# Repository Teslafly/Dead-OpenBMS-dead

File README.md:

THIS PROJECT IS DEAD. The avalibility of other projects and low cost off the shelf solutions has imporved significantly to where this project is no londer needed.

A much more mature open source bms that I recommend is https://github.com/EnnoidMe/ENNOID-BMS that has all the features that I had wanted to implement.
Off the shelf hardware is available for that too if you don't want to build your own.

Intro
==========
* This project aims to create an open source, scalable Battery management system for use in just about anything with more than 4 lithium batteries. (and currently up to 96 cells without a second master board)
* It aims to be as open source as possible so ideally all software should be free and unlimited. All PCB designs are done in KiCad (Using Fairly recent dev builds through Kicad Winbuilder) and all microcontroller programming is done in Arduino.

You can find a discussion thread for this project here on the Endless Sphere fourm: http://endless-sphere.com/forums/viewtopic.php?f=14&t=63863
Goals
==========
* Open source - It seems that almost all gms systems on the market are closed down these days. we want to be able to add whatever features we please as the EV world gets ever more integrated and complex
* Low cost - The BMS IC was selected to be as low cost as possible with a daisy chain approach used to further attempt to reduce costs through high manufacturing volume. Goal of $2 per cell can be reached. Master board may bump that up for smaller systems.
* Reliable - Even though a goal is to keep costs low, reliability should not be unnecessarily decreased for small cost improvements
* Safe - in going with reliable, I don't want this thing to start any fires or cause any damage. I want it to prevent any possible catastrophes associated with using such a power dense energy source.
* Easy to use - Board is programmed in the commonly known Arduino, but may use an rtos like chibios to facilitate low power-modes and can/usb tasks. Integration with a larger system could possibly be done with ladder logic programming.
* Multi chemistry - Can monitor and balance almost anything with "lithium" in the name. (lipo, lifepo4, etc. Possibly even super-capacitor banks)

Boards
===============
There are several boards contained within this project

* The Master board. it contains the mcu (The same microcontroller used in the teensy 3.1) The CAN transceiver and a couple other odds and ends such as a contactor driver.
* The MicroMaster board. This one contains an atmega328 with current sensing and little else. 
This board is meant as a lower cost alternative to the regular master board. It can also be used to control packs >96 cells by connecting it to a master via optoisolators.
* The daughter cell management board. It contains the voltage measuring ic and balancing resistors.
* The bus termination board. This one does precious little except ties the datapins of the top slave board together and allow activation of the system with an optoisolator.

Master Features (plannned)
===============
* Teensy 3.1 microcontroller (MK20DX256VLH7)
* USB programmable with a possibility of usb otg for android devices / dashboards. (and could charge phones/tablets with switching regulator)
* CAN transceiver for data connection to other modules.
* Connectors for an i2c/serial LCD dashboard and all extra pins broken out for auxiliary I/O.
* Input voltage sensing
* Switching voltage regulator to bring pack voltage down to 5-12v when system is on for auxiliary functions.
* 4 mosfet controlled low side outputs. These can be used to control a contactor, precharge circuit relay, fan, etc.
* 3 dedicated current sensor inputs. one for charging, one for the motor and one on-board for monitoring auxiliary systems.
* SD card slot for datalogging (and possible configuration via txt file)
* Analog and pwm throttle input & output. This can map the throttle to different values, change a analogue signal to a pwm one, or/and cut/hold back throttle when the pack is almost empty/dead.
* Opto isolators for controlling charger or communicating to voltage shifted masters.
* Buzzer / alarm - If something goes severely wrong, this board will let you know

MicroMaster Features - Implemented
===============
* Atmega328 main processor @ 3.3v - 8mhz. Programmable through arduino with usb -> serial adapter (Program it just like an Arduino pro mini)
* Runs completely off power output from slave board/s. This is convenient but allows no SD card or indicator leds as the ATA6870N can only supply 20ma
* 2 dedicated current sensor inputs. Useful for sensors like the ACS759
* 2 auxiliary 12-24v 5A NPN mosfets. (current is untested!) The voltage on this auxiliary rail is also monitored via a voltage divider. This is for controlling contactors, fans, etc
* 1 connector for a precharge circuit. Outputs for 1 small relay and a protected adc input for a controller voltage monitoring circuit.
* All other I/O pins are brought out to a 10 pin header along with 3.3v and GND. 

Slave Board Features (plannned)
===========
* Measures 4-6 Li-Ion Cells in Series 
* Stackable Architecture Enables >400V Systems (Up to 16 6s modules)). - (Micro)Master modules can be isolated and daisy chained  for even higher voltages 
* 0.25% Maximum Total Measurement Error (12 bit adc) - This will be tested in reality once the first boards are constructed.
* Extremely low power when asleep. (<100ua)
* Two Thermistor Inputs - One connected to an On-Board Temperature Sensor and the other one brought out to a header.
* temperature management. software will reduce the duty cycle of the balance resistors if the board gets too hot.

Cell Balancing:
==============
* Balancing achieved with ~20 ohm resistor banks. This means ~1 watt power of dissipation per cell. Heatsinking is probably needed at this level for full balancing current on all cells.
* An onboard thermistor will instruct the controller to reduce the duty cycle of the resistors in 25% increments (from 25-100%) to keep the board from overheating / melting.
* Predictive cell balancing? If a cell always needs a certain amount of energy removed while charging the board will pre-emptively balance the cell. I know of no example of this and will investigate its utility 

Software Goals
===========
* ~Readout of all individual cell voltages and analog inputs ~ DONE! (It could probably be made more efficient though)
* Manually control system outputs 
* Dataloggging, including current, cell voltages, and recording of total time the balance resistor has been on for each cell. useful for identifying weak/strong cells.
* Cell resistance estimate - use amperage draw and cell voltages to estimate cell resistances.
* Coulomb Counting for entire battery pack as well as cumulative coulumbs in/out for battery wear estimation

Photos
===========

![schematic] (https://raw.githubusercontent.com/Teslafly/OpenBMS/master/Docs/photos/Open%20source%20BMS.png)

TODO:
===============
* finish and post the micromaster board -Done!
* make a separate folder for all the kicad libraries and 3d models used in the project
* write a blog post on teslafly.wordpress.com detailing this project.
* make some prototypes ~ parts have arrived.

License
===========
GPL 3.0

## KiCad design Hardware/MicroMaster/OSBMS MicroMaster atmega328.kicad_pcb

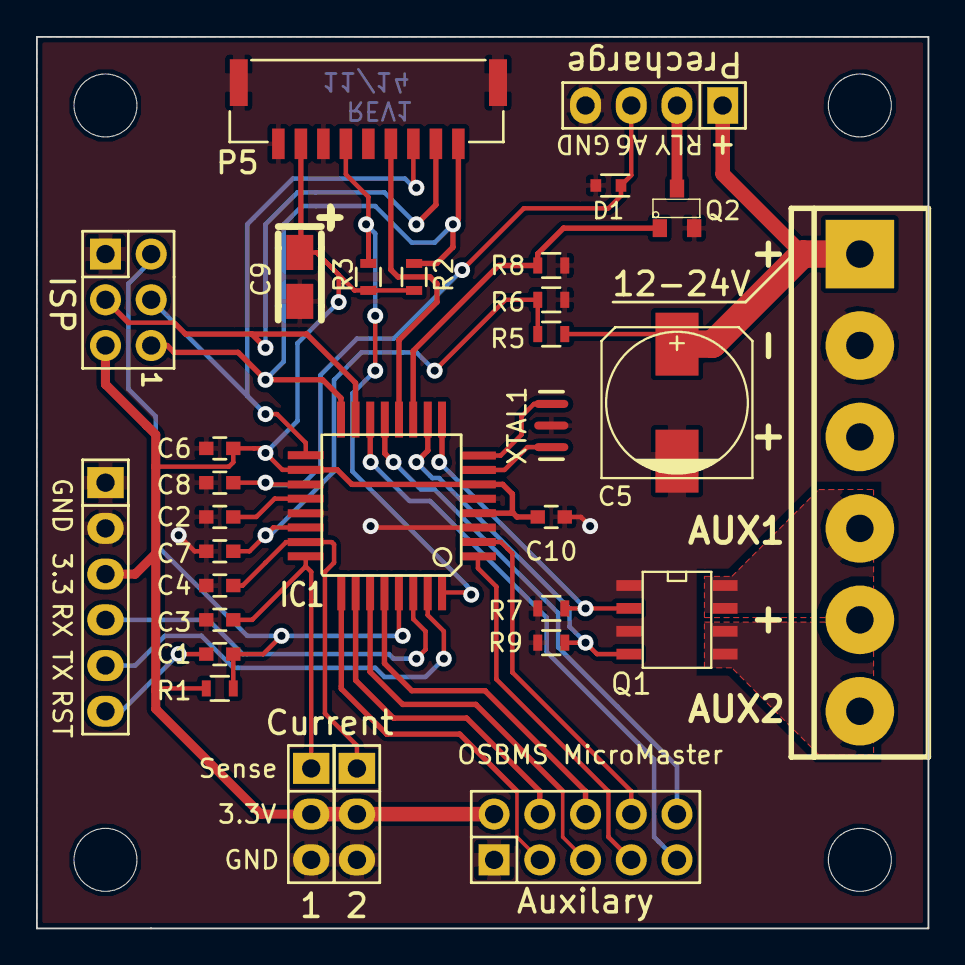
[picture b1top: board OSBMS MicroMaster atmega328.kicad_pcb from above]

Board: 2 copper layers, 49.5 x 49.5 mm, 35 parts (0 on the bottom side), 33 nets.

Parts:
C1, C2, C3, C4, C6, C7, C8: 100NF; C_0603
C5: CP1; c_elec_8x10
C9: 33uF PolC; TantalC_SizeA_EIA-3216_Reflow
C10: 100nF; C_0603
D1: 3.3vZENER; SOD-523
IC1: ATMEGA328P-A; TQFP-32
MH: MountingHole_3-5mm_RevA_Date21Jun2010; MountingHole_3-5mm
MH#2, MH#3, MH#4: MountingHole_3-5mm_RevA_Date21Jun2010; MountingHole_3-5mm
P1: CONN_01X06; Pin_Header_Straight_1x06
P2: CONN_02X03; Pin_Header_Straight_2x03
P3, P4: CONN_01X03; Pin_Header_Straight_1x03
P5: CONN_01X09; Connector_SMD_GH_SIDECONN_1X9_1.25MM
P6: CONN_01X10; Pin_Header_Straight_2x05
P7: CONN_01X06; bornier6
P10: CONN_01X04; Pin_Header_Straight_1x04
Q1: FDS6892A; SOIC-8-W
Q2: BSS138; SOT-23
R1, R2, R3, R7, R8, R9: 10K; R_0603
R5: 50k ohm; R_0603
R6: 5k ohm; R_0603
XTAL1: 8mhz resonator; RESONATOR-SMD-mutera

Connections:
400khz_clk: IC1.13, P5.5
+3.3V: C6.2, C9.1, C10.1, IC1.4, IC1.6, IC1.18, P1.3, P2.5, P3.2, P4.2, P5.8, P6.2, R1.2, R2.1, R3.1
+12V: C5.1, P7.1, P7.3, P7.5, P10.1, R5.2
/S-RST: C1.1, P1.6
A0: C4.2, IC1.23, P4.1
A1: C3.2, IC1.24, P3.1
A2: IC1.25, P6.3
A3: IC1.26, P6.4
A6: C8.2, D1.2, IC1.19, P10.3
A7: C7.2, IC1.22, R5.1, R6.2
CS_N: IC1.12, P5.4
D3*: IC1.1, P6.7
D4: IC1.2, P6.8
D5*: IC1.9, Q1.2, R7.2
D6*: IC1.10, Q1.4, R9.2
D7: IC1.11, Q2.1, R8.2
D10*: IC1.14, P6.9
GND: C2.1, C3.1, C4.1, C5.2, C6.1, C7.1, C8.1, C9.2, C10.2, D1.1, IC1.3, IC1.5, IC1.21, P1.2, P2.1, P3.3, P4.3, P5.7, P5.9, P6.1, P7.2, P10.4, Q1.1, Q1.3, Q2.2, R6.1, R7.1, R8.1, R9.1, XTAL1.2
Int0/2: IC1.32, P5.6, R3.2
MISO: IC1.16, P2.6, P5.1, R2.2
MOSI: IC1.15, P2.3, P5.2
unnamed: C2.2, IC1.20
unnamed: IC1.7, XTAL1.3
unnamed: IC1.8, XTAL1.1
unnamed: P7.4, Q1.7, Q1.8
unnamed: P7.6, Q1.5, Q1.6
unnamed: P10.2, Q2.3
RESET: C1.2, IC1.29, P2.2, R1.1
RXD: IC1.30, P1.4
SCK/13: IC1.17, P2.4, P5.3
SCL/A5: IC1.28, P6.6
SDA/A4: IC1.27, P6.5
TXD: IC1.31, P1.5

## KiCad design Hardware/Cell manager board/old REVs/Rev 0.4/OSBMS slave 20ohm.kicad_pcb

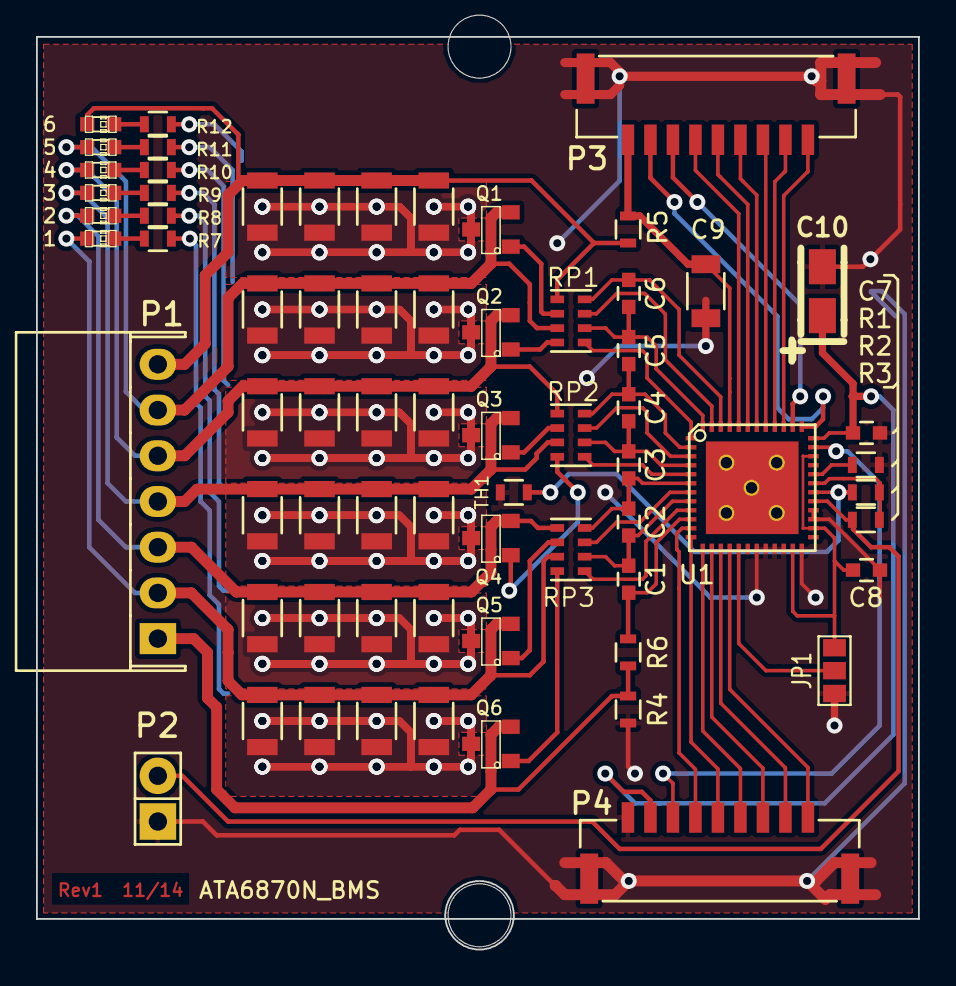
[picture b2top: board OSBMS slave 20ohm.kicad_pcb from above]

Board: 2 copper layers, 49.0 x 50.7 mm, 76 parts (1 on the bottom side), 63 nets.

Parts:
28 mil Id via, 28 mil Id via#2, 28 mil Id via#3, 28 mil Id via#4, 28 mil Id via#5: via; 35-Od-28mil-Id-via
C1, C2, C3, C4, C5, C6, C7, C8: 100nF; C_0603
C9: 10uF PolC; C_1206
C10: 33uF PolC; TantalC_SizeA_EIA-3216_Reflow
D1, D2, D3, D4, D5, D6: LED; LED-0603
JP1: JUMPER3; GS3
MH: MountingHole_3-5mm_RevA_Date21Jun2010; MountingHole_3-5mm
MH#2: MountingHole_3-5mm_RevA_Date21Jun2010; MountingHole_3-5mm
P1: CONN_01X07; Shrouded_Header_Angled_1x07
P2: EXT-TMP; Pin_Header_Straight_1x02
P3, P4: CONN_01X09; Connector_SMD_GH_SIDECONN_1X9_1.25MM_45515711ND
P5: CONN_01X01; 1Pin
Q1, Q2, Q3, Q4, Q5, Q6: BSS138; SOT-23
R1: 121KΩ; R_0603
R2, R3: 10KΩ; R_0603
R4, R5: 10Ω; R_0603
R6: 1K; R_0603
R7, R8, R9, R10, R11, R12: 100Ω; R_0603
R13, R20, R21, R22, R23, R24, R25, R26, R27, R28, R29, R30, R31, R32, R33, R34, R35, R36, R37, R38, R39, R40, R41, R42: 82.5Ω; R_1206
RP1, RP2, RP3: 1K_PACK; R_Cat16-4
TH1: THERMISTOR; R_0603
U1: ATA6870N_BMS; QFN-48-1EP

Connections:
+3.3V: C7.1, C10.1, P4.2, U1.36
+BATT: C9.1, P3.9, R5.1, U1.45
/DISCH1: RP3.5, U1.9
/DISCH2: RP3.7, U1.7
/DISCH3: RP2.5, U1.5
/DISCH4: RP2.7, U1.3
/DISCH5: RP1.5, U1.1
/DISCH6: RP1.7, U1.47
GND: C7.2, C8.2, C9.2, C10.2, JP1.3, P2.1, P4.1, R1.1, R4.1, TH1.2, U1.19, U1.20, U1.21, U1.22, U1.24, U1.27, U1.28
unnamed: C1.1, C2.2, RP3.6, U1.8
unnamed: C1.2, R6.1, U1.10
unnamed: C2.1, C3.2, RP3.8, U1.6
unnamed: C3.1, C4.2, RP2.6, U1.4
unnamed: C4.1, C5.2, RP2.8, U1.2
unnamed: C5.1, C6.2, RP1.6, U1.48
unnamed: C6.1, RP1.8, U1.46
unnamed: C8.1, JP1.1, U1.23, U1.26, U1.34
unnamed: D1.1, P1.7, R5.2, R20.1, R21.1, R22.1, R23.1, RP1.1
unnamed: D1.2, R12.2
unnamed: D2.1, P1.6, Q1.2, R24.1, R25.1, R26.1, R27.1, RP1.3
unnamed: D2.2, R11.2
unnamed: D3.1, P1.5, Q2.2, R28.1, R29.1, R30.1, R31.1, RP2.1
unnamed: D3.2, R10.2
unnamed: D4.1, P1.4, Q3.2, R13.1, R32.1, R33.1, R34.1, RP2.3
unnamed: D4.2, R9.2
unnamed: D5.1, P1.3, Q4.2, R35.1, R36.1, R37.1, R38.1, RP3.1
unnamed: D5.2, R8.2
unnamed: D6.1, P1.2, Q5.2, R39.1, R40.1, R41.1, R42.1, RP3.3
unnamed: D6.2, R7.2
unnamed: JP1.2, U1.17
unnamed: P1.1, Q6.2, R4.2, R6.2
unnamed: P2.2, R3.2, U1.29
unnamed: P3.1, U1.39
unnamed: P3.2, U1.40
unnamed: P3.3, U1.41
unnamed: P3.4, U1.42
unnamed: P3.5, U1.43
unnamed: P3.6, U1.44
unnamed: P3.7, U1.38
unnamed: P3.8, U1.37
unnamed: P4.3, U1.35
unnamed: P4.4, U1.11
unnamed: P4.5, U1.12
unnamed: P4.6, U1.13
unnamed: P4.7, U1.14
unnamed: P4.8, U1.15
unnamed: P4.9, U1.16
unnamed: Q1.1, RP1.2
unnamed: Q1.3, R12.1, R20.2, R21.2, R22.2, R23.2
unnamed: Q2.1, RP1.4
unnamed: Q2.3, R11.1, R24.2, R25.2, R26.2, R27.2
unnamed: Q3.1, RP2.2
unnamed: Q3.3, R10.1, R28.2, R29.2, R30.2, R31.2
unnamed: Q4.1, RP2.4
unnamed: Q4.3, R9.1, R13.2, R32.2, R33.2, R34.2
unnamed: Q5.1, RP3.2
unnamed: Q5.3, R8.1, R35.2, R36.2, R37.2, R38.2
unnamed: Q6.1, RP3.4
unnamed: Q6.3, R7.1, R39.2, R40.2, R41.2, R42.2
unnamed: R1.2, U1.32
unnamed: R2.1, R3.1, U1.31
unnamed: R2.2, TH1.1, U1.30
ThermalGnd: 28 mil Id via.1, 28 mil Id via#2.1, 28 mil Id via#3.1, 28 mil Id via#4.1, 28 mil Id via#5.1, P5.1

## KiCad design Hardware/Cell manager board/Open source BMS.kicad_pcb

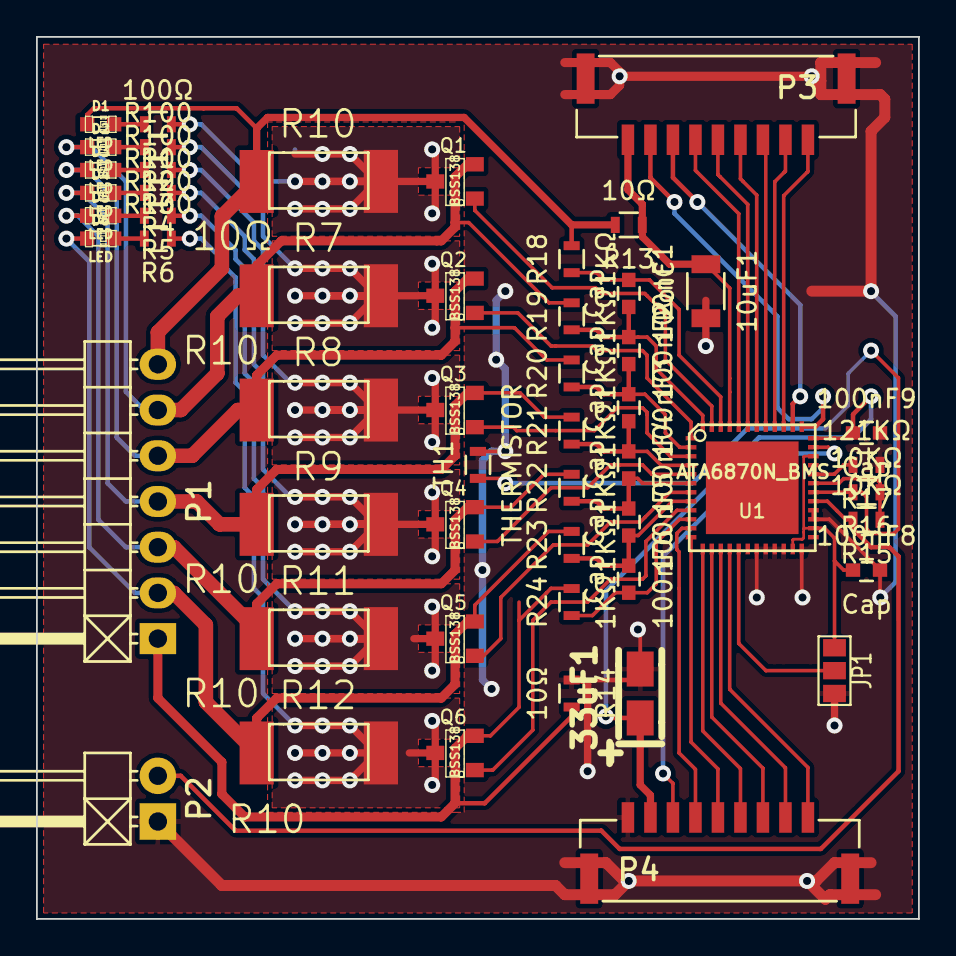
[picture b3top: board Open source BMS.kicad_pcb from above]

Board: 2 copper layers, 49.0 x 49.0 mm, 53 parts (0 on the bottom side), 56 nets.

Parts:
10uF1: PolC; C_1206
33uF1: PolC; TantalC_SizeA_EIA-3216_Reflow
100nF1, 100nF2, 100nF3, 100nF4, 100nF5, 100nF6, 100nF8, 100nF9: Cap; C_0603
D1, D2, D3, D4, D5, D6: LED; LED-0603
JP1: JUMPER3; GS3
P1: CONN_01X07; Pin_Header_Angled_1x07
P2: EXT-TMP; Pin_Header_Angled_1x02
P3, P4: CONN_01X09; Connector_SMD_GH_SIDECONN_1X9_1.25MM_45515711ND
Q1, Q2, Q3, Q4, Q5, Q6: BSS138; SOT-23
R1: 100Ω; R_0603
R2, R3, R4, R5, R6: R100; R_0603
R7, R8, R9, R11, R12: R10; R_3521
R10: 10Ω; R_3521
R13, R14: 10Ω; R_0603
R15, R16: 10KΩ; R_0603
R17: 121KΩ; R_0603
R18, R19, R20, R21, R22, R23, R24: 1KΩ; R_0603
TH1: THERMISTOR; R_0603
U1: ATA6870N_BMS; QFN-48-1EP

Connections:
+3.3V: 33uF1.1, 100nF9.1, P4.2, U1.36
+BATT: 10uF1.1, P3.9, R13.1, U1.45
/DISCH1: Q6.1, U1.9
/DISCH2: Q5.1, U1.7
/DISCH3: Q4.1, U1.5
/DISCH4: Q3.1, U1.3
/DISCH5: Q2.1, U1.1
/DISCH6: Q1.1, U1.47
GND: 10uF1.2, 33uF1.2, 100nF8.2, 100nF9.2, JP1.3, P2.1, P4.1, R14.1, R17.1, TH1.2, U1.19, U1.20, U1.21, U1.22, U1.24, U1.27, U1.28
unnamed: 100nF1.1, R18.1, U1.46
unnamed: 100nF1.2, 100nF2.1, R19.1, U1.48
unnamed: 100nF2.2, 100nF3.1, R20.1, U1.2
unnamed: 100nF3.2, 100nF4.1, R21.1, U1.4
unnamed: 100nF4.2, 100nF5.1, R22.1, U1.6
unnamed: 100nF5.2, 100nF6.1, R23.1, U1.8
unnamed: 100nF6.2, R24.1, U1.10
unnamed: 100nF8.1, JP1.1, U1.23, U1.26, U1.34
unnamed: D1.1, P1.7, R10.1, R13.2, R18.2
unnamed: D1.2, R1.2
unnamed: D2.1, P1.6, Q1.2, R7.1, R19.2
unnamed: D2.2, R2.2
unnamed: D3.1, P1.5, Q2.2, R8.1, R20.2
unnamed: D3.2, R3.2
unnamed: D4.1, P1.4, Q3.2, R9.1, R21.2
unnamed: D4.2, R4.2
unnamed: D5.1, P1.3, Q4.2, R11.1, R22.2
unnamed: D5.2, R5.2
unnamed: D6.1, P1.2, Q5.2, R12.1, R23.2
unnamed: D6.2, R6.2
unnamed: JP1.2, U1.17
unnamed: P1.1, Q6.2, R14.2, R24.2
unnamed: P2.2, R15.2, U1.29
unnamed: P3.1, U1.39
unnamed: P3.2, U1.40
unnamed: P3.3, U1.41
unnamed: P3.4, U1.42
unnamed: P3.5, U1.43
unnamed: P3.6, U1.44
unnamed: P3.7, U1.38
unnamed: P3.8, U1.37
unnamed: P4.3, U1.35
unnamed: P4.4, U1.11
unnamed: P4.5, U1.12
unnamed: P4.6, U1.13
unnamed: P4.7, U1.14
unnamed: P4.8, U1.15
unnamed: P4.9, U1.16
unnamed: Q1.3, R1.1, R10.2
unnamed: Q2.3, R2.1, R7.2
unnamed: Q3.3, R3.1, R8.2
unnamed: Q4.3, R4.1, R9.2
unnamed: Q5.3, R5.1, R11.2
unnamed: Q6.3, R6.1, R12.2
unnamed: R15.1, R16.1, U1.31
unnamed: R16.2, TH1.1, U1.30
unnamed: R17.2, U1.32

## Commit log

2014-09-26 :boom::camel: Added .gitattributes & .gitignore files
2014-09-26 Preliminary commit
    schematic and readme added
2014-09-27 progress
    Mostly put together but missing traces
2014-10-02 board rev1 finished except for silkscreen
    bms slave board finished excluding silkscreen
2014-10-02 updated readme and minor file structure changes
    ditto
2014-10-02 forgot stuff
    ditto
2014-10-06 updated documentation
    some updated documentation files and readme. preliminary BOM added
2014-10-06 Changed 10uf cap and added slave BOM
    Changed the 10uf cap to one that is slightly smaller and 1/5th the
    price. (at the expense of voltage, 100v>35v) Also added a BOM for the
    Cell manager slave board with all parts but the thermistor and
    assosiated resistors
2014-10-07 added schematic pictures and brushed up labels
    ditto
2014-10-07 updated bom with 1 unit pricing
    ditto
2014-10-08 cleaned up silkscreen and improved readme
    Improved the readme file and added MicroMaster board to it. Also cleaned
    up the Slave balance board's silkscreen
2014-10-12 changing resistor design
    changing resistor design to be cheaper to make and put out a more
    manageable amount of heat.
    previous design archived
2014-10-13 changed design to use better resistors
    revamped design to use more commonly avalable resistors and resistor
    packs that should protect the mosfet gates in the event of a voltage
    spike etc. also improved thermal design. some thermal stitching still
    has to be done but is quite tedious
2014-10-14 finished resistor change and via stiching
    finished resistor change and via stiching. board is now functional (at
    least I hope) the last thing to do is tidy up the silkscreen and
    soldermask
2014-11-09 Completed preliminary test program
    created a test program that reads cell voltages out to serial (raw adc
    values, not scaled voltages). this sketch also contains a lot of
    partially working functions for future functionality.
    also updated was the atmega328 based master board. - which is not quite
    complete
2014-11-13 Fixed test code and schematic
    Fixed a problem in the code that caused it to hang. spi now appears to
    be working porperly with a logic analyzer. I also finished up some
    stuff with the micromaster schematic. It is now ready to be laied out on
    a pcb
2014-11-13 Actually fixed code
    The last commit had a mistake and this commit actually fixes the program
    as well as advancing slightly on the micromaster design
2014-11-16 touched up balancer board and reorganised
    touched up balancer board so that it is ready for production,
    reorganised a bunch of files and added proper revision labels, and made
    good progress on the micromaster board. the schematic is complete, the
    board is layed out, some traces still need to be run though.
2014-11-18 Rev1 READY!
    All the boards have been completed and arre ready for prototype
    production. docunentation has been updated and the docs folder now
    contains schematic pdf's, rendered pictures, and completed bill of
    materials for both boarrds.
    The software also recieved an update that corrected a datatype error and
    shouuld make it testing ready.
2014-12-31 Finalised V1 for production
    Finalised V1 for production. added hot symbol, moved mounting holes to
    better location, fixed remaining drc error, and tiedied up silkscreen
2015-01-03 Many little changes.
    many little changes, mostly in the code comments and very little in
    actual functionality. (much more framework that isn't being used has
    been added though) goals have been refined and files moved around
    slightly. This is in perperation for easier usability and contribution
    by others.
2015-01-14 Checksum working
    Checksum function is now working. spi read/write functions have been
    revamped and the function for controlling cell balance resistors has
    been implemented. sketch header todo's and readme have been updated
    accordingly.
2015-01-18 Reworked SPI functions
    Reworked SPI functions and compined read and write into a single
    function.
    made appropriate changes in all other functions and added more error
    checking.
    also added a small loop to test the cell balance resistors one at a
    time.
2015-01-29 Hardware Tested
    hardware tested. cell balancer routine, calibration and cell voltage
    data routines are working in software v2.0. spi should be mostly
    finished with the exception of checksum and power optimisations.
2015-02-03 Balancing operational
    Added new sketch "balancer" which can balance batteries to the lowest
    cell voltage. This is tested.
2016-05-10 work dump
    board schematics should be working. may include some unfinished
    schematics and software pieces
2017-01-18 Update README.md
    Reformat to markdown..
    Any plans for future.
2022-01-16 Update README.md
    dead
2023-01-18 Forward people to enoid bms.
